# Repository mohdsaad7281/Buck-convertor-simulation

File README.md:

# Buck Converter — Design, Simulation & PCB Layout

A 12V → 5V DC-DC buck converter, taken from hand calculation through LTspice simulation to a manufacturable PCB layout in KiCad.

## Specifications

| Parameter                       | Target               |
| -------------------------------- | -------------------- |
| Input voltage (Vin)             | 12 V                 |
| Output voltage (Vout)           | 5 V                  |
| Load current (Iout)             | 1 A                  |
| Switching frequency (fs)        | 100 kHz              |
| Duty cycle (D)                  | ≈ 0.417              |
| Inductor ripple current (ΔI_L)  | 0.2 A (target)        |
| Output voltage ripple (ΔV_out)  | 50 mV / ~1% (target)  |

---

## Part 1: Design & Simulation (LTspice)

### Design approach

The converter was designed from first principles rather than picking arbitrary component values:

1. **Duty cycle** was calculated from the ideal buck relationship: D = Vout / Vin
2. **Inductance** was sized to keep inductor ripple current at a target 20% of load current, using:
   L = (Vin − Vout) × D / (ΔI_L × fs)
3. **Output capacitance** was sized to keep output ripple voltage near 1% of Vout, using:
   C = ΔI_L / (8 × fs × ΔV_out)

This gave calculated values of **L ≈ 146 µH** and **C ≈ 5 µF**, which were then used to build and simulate the circuit rather than just left as theoretical numbers.

### Circuit

Built in LTspice using:

- An ideal voltage-controlled switch (`SW`), driven by a `PULSE` source acting as the PWM gate signal
- A freewheeling diode for the inductor current path when the switch is off
- LC output filter (L1, C1) and a resistive load (R1 = 5Ω, sized for 1A at 5V)

Switch model:

```
.model SW1 SW(Ron=0.01 Roff=1Meg Vt=2.5 Vh=0.1)
```

PWM drive:

```
PULSE(0 5 0 10n 10n 4.17u 10u)
```

### Results

Measured via `.tran` transient simulation and `.meas` directives on steady-state waveforms:

| Metric                            | Value        |
| ---------------------------------- | ------------ |
| Output voltage (Vout)             | ≈ 4.53 V     |
| Average inductor current (IL_avg) | ≈ 0.91 A     |
| Input power (Pin)                 | ≈ 4.54 W     |
| Output power (Pout)               | ≈ 4.10 W     |
| **Efficiency**                    | **≈ 90.3 %** |

- Output voltage settled close to the 5V target; the small gap (~0.47 V) is attributable to non-ideal switch on-resistance and diode forward voltage drop, which aren't captured in the ideal hand calculation.
- Inductor current showed a clean, repeating sawtooth ripple centered near the 1A design load, confirming steady-state operation matched the design intent.
- The ~9.7% power loss is consistent with conduction loss in the switch (Ron) and forward-voltage drop across the freewheeling diode — both of which are excluded from the idealized hand-calculated design.

### Simulation files

- `buckconvertor.asc` — LTspice schematic
- `waveforms/` — simulation output screenshots (Vout settling, inductor current ripple)

---

## Part 2: PCB Design (KiCad)

To take the design beyond simulation, I laid out a real printed circuit board in KiCad, translating the same buck converter topology into a manufacturable design.

### Design approach

Rather than replicating the idealized switch from the LTspice simulation, I designed around the **LM2596S-5.0**, an industry-standard integrated buck regulator IC. This kept the physical topology consistent with the simulated circuit (the same external inductor, freewheeling diode, and output capacitor filter) while avoiding the added complexity of a discrete MOSFET + gate driver + compensator design, which was outside the scope of what I wanted this project to defend in depth.

**Bill of Materials:**

| Ref | Part | Value/Rating |
| --- | --- | --- |
| U1 | LM2596S-5.0/NOPB | TO-263-5, fixed 5V, 3A |
| L1 | Shielded power inductor | 33–68 µH, ≥3A saturation |
| D1 | Schottky diode | 1N5822 / SS34, 3A |
| Cin | Electrolytic | 100 µF |
| Cout | Low-ESR electrolytic | 100–220 µF |
| J1, J2 | 2-pin terminal block | 5mm pitch |

### Layout considerations

The most important layout decision was minimizing the **power loop** — the high di/dt switching path formed by U1's OUT pin, D1, and L1. This loop was routed as short and tight as possible to limit EMI and voltage ringing at the switch node, with input and output capacitors placed immediately adjacent to the pins they filter.

The board uses a 2-layer stackup with a solid ground pour on the bottom copper layer. Since component GND pads sit on the top layer while the ground plane is on the bottom, I added stitching vias at each GND pad to tie the two together — without them, ERC/DRC correctly flagged these as disconnected "islands," which was a useful reminder that a ground plane doesn't automatically connect to pads on a different layer.

Trace widths on the power path (VIN, switch node, Vout, GND) were sized using the IPC-2221 current-carrying capacity formula for ~2A on 1oz copper at a 10°C temperature rise, rather than left at default.

### What I'd flag if building this for real

- The footprint used for L1 is a placeholder — a real build would use the exact manufacturer footprint for a chosen shielded power inductor (e.g. Bourns SRN6045-330M).
- The LM2596's internal switching frequency (~150kHz) differs from the 100kHz PWM used in the LTspice simulation, since the IC has its own fixed oscillator rather than the externally-driven ideal switch modeled earlier.

### PCB files

- `pcb/buck_convertor.kicad_pro`, `.kicad_sch`, `.kicad_pcb` — full KiCad project
- `pcb/gerbers.zip` — Gerber + drill files, fab-ready
- `pcb/BOM.csv` — bill of materials
- `pcb/images/` — schematic, routed layout, and 3D render screenshots

This is a design-only deliverable — the board has not been fabricated or assembled.

---

## Tools

LTspice (SPICE circuit simulation), KiCad (schematic capture & PCB layout)

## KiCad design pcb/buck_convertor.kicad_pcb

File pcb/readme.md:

PCB design files for the buck converter — schematic, layout, Gerbers, and BOM.

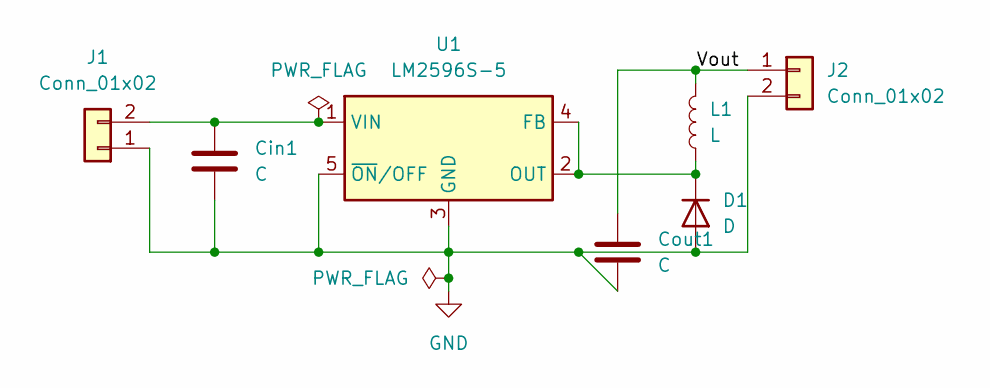
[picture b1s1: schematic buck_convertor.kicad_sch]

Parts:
Cin1: C; CP_Elec_6.3x5.3
Cout1: C; CP_Elec_6.3x5.3
D1: D; D_SMA
J1, J2: Conn_01x02; TerminalBlock_MaiXu_MX126-5.0-02P_1x02_P5.00mm
L1: L; L_1812_4532Metric
U1: LM2596S-5; TO-263-5_TabPin3

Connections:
/Vout: Cout1.2, J2.1, L1.2
GND: Cin1.1, Cout1.1, D1.2 (A), J1.1, J2.2, U1.3 (GND), U1.5 (~ON/OFF)
unnamed: D1.1 (K), L1.1, U1.2 (OUT), U1.4 (FB)
unnamed: Cin1.2, J1.2, U1.1 (VIN)

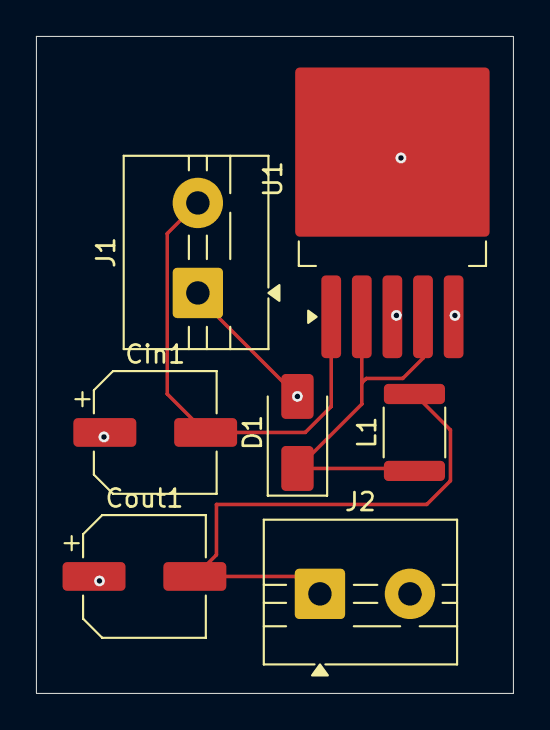
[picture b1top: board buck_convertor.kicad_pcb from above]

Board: 2 copper layers, 26.5 x 36.5 mm, 7 parts (0 on the bottom side), 4 nets.

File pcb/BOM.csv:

"Reference","Qty","Value","DNP","Exclude from BOM","Exclude from Board","Exclude from Simulation","Exclude from Position Files","Footprint","Datasheet"
"Cin1,Cout1","2","C","","","","","${EXCLUDE_FROM_POS_FILES}","Capacitor_SMD:CP_Elec_6.3x5.3",""
"D1","1","D","","","","","${EXCLUDE_FROM_POS_FILES}","Diode_SMD:D_SMA",""
"J1,J2","2","Conn_01x02","","","","","${EXCLUDE_FROM_POS_FILES}","TerminalBlock:TerminalBlock_MaiXu_MX126-5.0-02P_1x02_P5.00mm",""
"L1","1","L","","","","","${EXCLUDE_FROM_POS_FILES}","Inductor_SMD:L_1812_4532Metric",""
"U1","1","LM2596S-5","","","","","${EXCLUDE_FROM_POS_FILES}","Package_TO_SOT_SMD:TO-263-5_TabPin3","http://www.ti.com/lit/ds/symlink/lm2596.pdf"
